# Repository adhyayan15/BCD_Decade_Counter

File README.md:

# BCD Decade Counter PCB

A breadboard circuit I turned into a PCB to get more comfortable with digital electronics and KiCad.

This started with a pretty simple goal: **make a 7-segment display count from 0 to 9 without using a microcontroller.** I first wired the circuit on a breadboard, checked that the counter worked, and then tried to fit the same idea onto a board I could design myself.

The interesting part wasn't the counting. It was figuring out how the clock, counter, decoder, resistors, and display all needed to connect, then translating that into an actual PCB layout.

## How it works

```text
NE555 timer (clock)
        |
        v
74LS90 decade counter (0–9)
        |
        v
4511 BCD-to-7-segment decoder
        |
        v
7-segment display (HDSP-7503)
```

The **NE555** provides the pulses. The **74LS90** counts them through the ten decimal states. The **4511** translates the BCD output into signals for the display. Seven **220 Ω resistors** limit current through the display segments.

The KiCad schematic also includes a **1 kΩ resistor, a 10 kΩ resistor, a polarized capacitor, and a two-pin power connection**. I used an external **5 V breadboard power module** during prototyping rather than designing a regulator onto this board.

## From breadboard to PCB

| PCB layout | Schematic |
| :---: | :---: |
|  |  |

After getting the breadboard circuit running, I redrew it in KiCad, assigned the through-hole footprints, and routed the board. This was a useful introduction to how much more deliberate you have to be once your wires become copper traces.

The schematic and board files are in [KiCad/](KiCad/). Open `BCD Decade Counter.kicad_pro` in KiCad to see or edit the actual design.

## Where it stands

- **Breadboard:** built and tested.
- **Schematic and PCB layout:** completed.
- **ERC/DRC:** passed during my design work.

I'm leaving the project as it is for now. It was a small circuit, but it was an important step in going from *connecting components* to designing the board those components sit on.

Built by **Adhyayan Tiwari** · [MIT License](LICENSE)

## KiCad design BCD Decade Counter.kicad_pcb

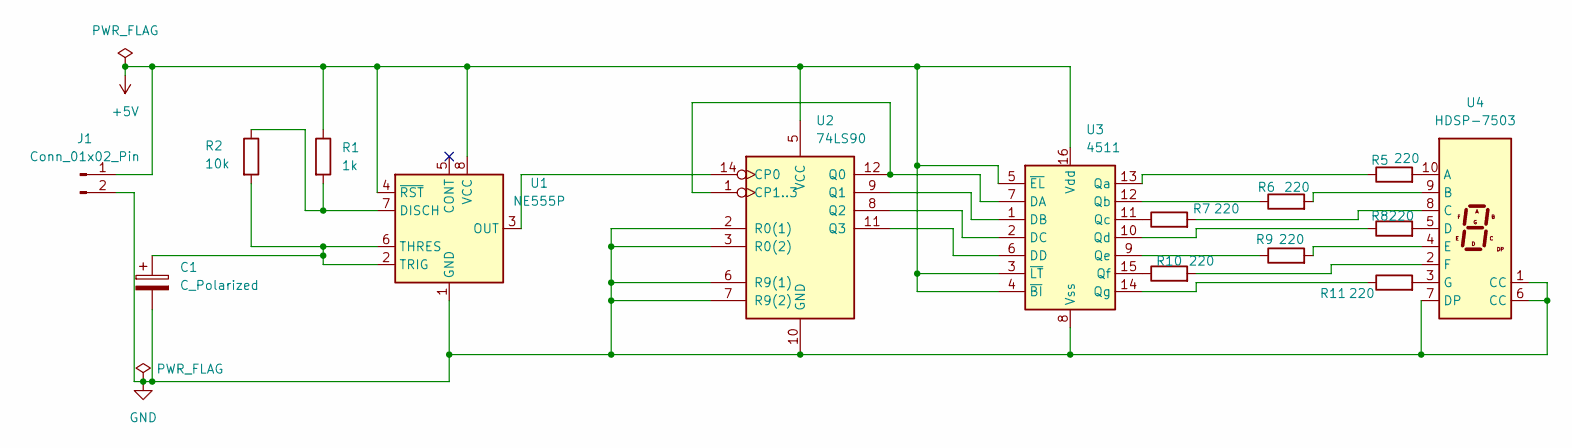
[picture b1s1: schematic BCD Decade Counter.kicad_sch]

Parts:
C1: C_Polarized; CP_Radial_D5.0mm_P2.00mm
J1: Conn_01x02_Pin; TerminalBlock_MaiXu_MX126-5.0-02P_1x02_P5.00mm
R1: 1k; R_Axial_DIN0207_L6.3mm_D2.5mm_P7.62mm_Horizontal
R2: 10k; R_Axial_DIN0207_L6.3mm_D2.5mm_P7.62mm_Horizontal
R5, R6, R7, R8, R9, R10, R11: 220; R_Axial_DIN0207_L6.3mm_D2.5mm_P7.62mm_Horizontal
U1: NE555P; DIP-8_W7.62mm
U2: 74LS90; DIP-14_W7.62mm
U3: 4511; DIP-16_W7.62mm
U4: HDSP-7503; HDSP-7507

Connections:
+5V: J1.1, R1.1, U1.4 (~RST), U1.8 (VCC), U2.5 (VCC), U3.3 (~LT), U3.4 (~BI), U3.5 (~EL), U3.16 (Vdd)
GND: C1.2, J1.2, U1.1 (GND), U2.2 (R0(1)), U2.3 (R0(2)), U2.6 (R9(1)), U2.7 (R9(2)), U2.10 (GND), U3.8 (Vss), U4.1 (CC), U4.6 (CC), U4.7 (DP)
unnamed: R1.2, R2.1, U1.7 (DISCH)
unnamed: U1.3 (OUT), U2.14 (CP0)
unnamed: C1.1, R2.2, U1.2 (TRIG), U1.6 (THRES)
unnamed: U2.1 (CP1..3), U2.12 (Q0), U3.7 (DA)
unnamed: U2.9 (Q1), U3.1 (DB)
unnamed: U2.8 (Q2), U3.2 (DC)
unnamed: U2.11 (Q3), U3.6 (DD)
unnamed: R5.1, U3.13 (Qa)
unnamed: R6.1, U3.12 (Qb)
unnamed: R7.1, U3.11 (Qc)
unnamed: R8.1, U3.10 (Qd)
unnamed: R9.1, U3.9 (Qe)
unnamed: R10.1, U3.15 (Qf)
unnamed: R11.1, U3.14 (Qg)
unnamed: R5.2, U4.10 (A)
unnamed: R6.2, U4.9 (B)
unnamed: R7.2, U4.8 (C)
unnamed: R8.2, U4.5 (D)
unnamed: R9.2, U4.4 (E)
unnamed: R10.2, U4.2 (F)
unnamed: R11.2, U4.3 (G)

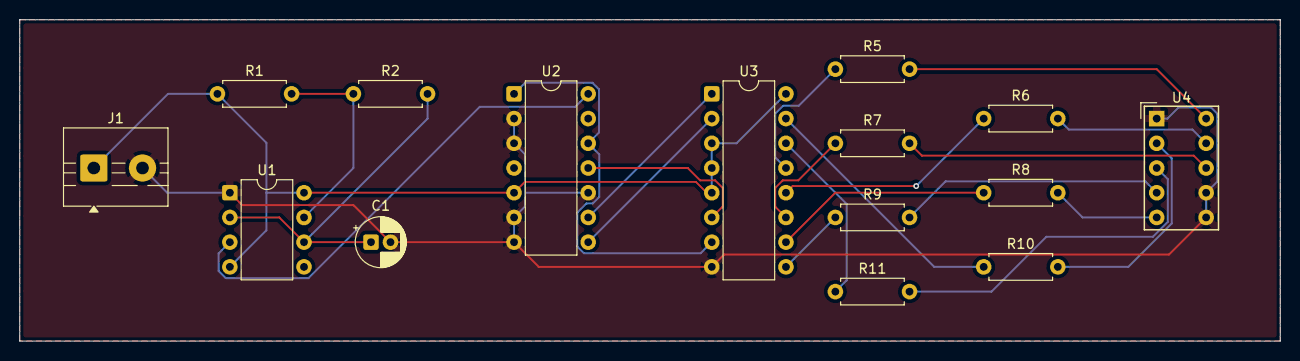
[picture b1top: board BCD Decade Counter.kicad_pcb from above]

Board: 2 copper layers, 129.5 x 33.0 mm, 15 parts (0 on the bottom side), 23 nets.
